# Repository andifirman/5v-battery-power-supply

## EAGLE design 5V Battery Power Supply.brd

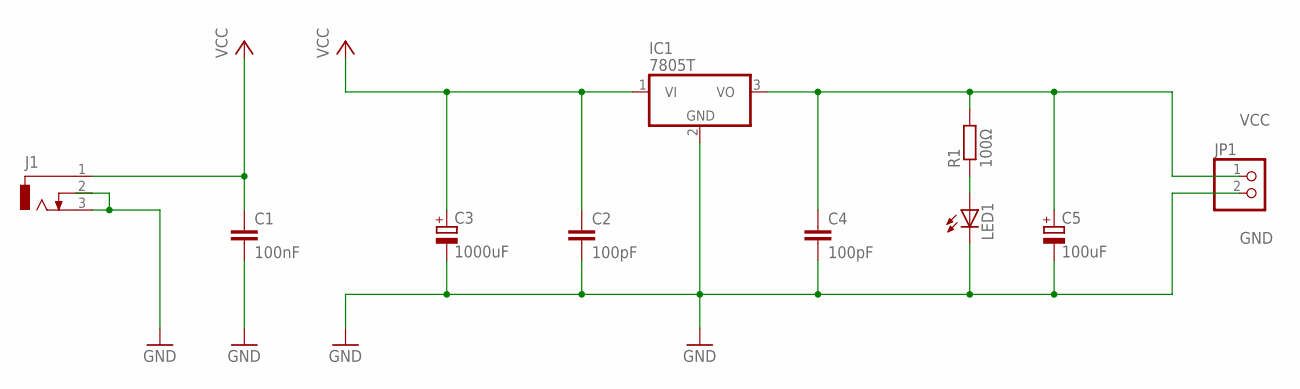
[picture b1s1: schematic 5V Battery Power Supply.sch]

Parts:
C1: 100nF; C025-050X050
C2, C4: 100pF; C025-050X050
C3: 1000uF; E2-5
C5: 100uF; E2-5
IC1: 7805T; TO220H
J1: DCJ0303
JP1: PINHD-1X2; 1X02
LED1: LED5MM
R1: 100Ω; 0207/7

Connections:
GND: C1.2, C2.2, C3.-, C4.2, C5.-, IC1.2 (GND), J1.3, JP1.2, LED1.K (C)
unnamed: LED1.A, R1.1
VCC: C1.1, C2.1, C3.+, C4.1, C5.+, IC1.1 (VI), IC1.3 (VO), J1.1, JP1.1, R1.2

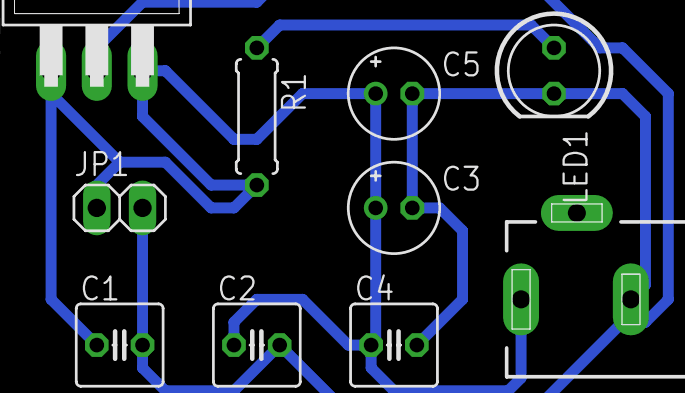
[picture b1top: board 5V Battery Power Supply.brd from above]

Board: 2 copper layers, 10 parts (0 on the bottom side), 3 nets.

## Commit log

2023-02-11 Add files via upload
    Schematic for 5V power supply.
2023-02-14 Adding board to repository
    The board is ready to print :D
